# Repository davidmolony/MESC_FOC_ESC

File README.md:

# MESC_FOC_ESC
MESC, Molony ESC, STM32F303 based FOC+BLDC ready, HALL, Encoder, Sensorless, single sides, 2 layer, ~90A @48V

This ESC is intended as a cost optimised alternative to the VESC, by utilising:

Standalone, industry standard footprint gate drivers

Standard D2PAK or H2PAK FETs

Cheap (~2.5$) STM32F303CB microcontroller

Board dimensions 100mmx50mm, so that it can be panelised and manufactured by JLCPCB, or two boards can be combined into one 100mm2 JLCPCB

It is not cross compatible with VESC software, and does not intend to be. VESC has run away with itself in terms of cost, firmware abstraction... in the opinion of this project's author.

# Current Status:  
First build has been made. All functions... function.
Photos in folder! Video of prelim run to be added to Youtube.
Step down works
Step up for Gate drives works
Chip works, all inputs and outputs works
Some concerns about stability of internal opamps... Returning 1.5V instead of 1.6V. First chip soldered returned 1V, and fluctuated by +0.3/-0.1V. 
Motor spins in BLDC mode (6 step) with hall sensors, on Propdrive 2826 1200kV and with APS8072 50kV. Current run up to 20A phase, with minimal PCB heating with no heatsink. Only run to 23V so far, owing to PSU limitation.
FET switching time rather slow with 5 ohm resistors, limiting peak current to 2A (not counting FET and Gate drive resistance) will reduce to 2R7.

# Layout:  
Layout optimised to minimise current loop path, and keep the board completely single sided assembly.

For thermal management, the FETs have vias underneath the drains, which can be interfaced with a heatsink on the PCB underside, using silicone pad/thermal paste & insulator.

# MCU uses:
Timer1 on PA8,9,10 (high) and PB13,14,15 for PWM generation.

Onboard opamps for current sensing and paralelled comparators input on pins PA1,7, PB0.

Phase voltages can be measured on PA3,4,5, or alternatively, digitally read to detect ZC .

Main voltage can be read on PA0.

# Interfaces:
External Interfaces include Hall/Encoder, I2C, PWM in, UART, USB FS.

Hall sensors on Timer4 PB6,7,8, alternatively Encoder can be run on Tim4 PB6,7

Timer3 channel 1 for standard RC PWM input.

USART3 Tx Rx on PB10,11.
USB on PA11,12, with 1k5 pullup to signal FS mode. Canbe used for reflashing (hypothetically).

I2C1 on PA15(SCL) and PB9(SDA), with a plug for a standard SSD1306 breakout. Alternatively, inertial sensor board could be plugged on breakout wire.

Expected BoM cost:  
0.4USD board  
6x2USD FETs  
2.5USD MCU  
3x1USD gate drives  
1USD SMPS converter  
0.4USD inductor  
??? connector cost (dependent on what's fitted, wire in...)  
0.3USD linear reg  
~3USD caps (dependent on how many you want to solder on, which is dependent on distance to battery, desire to comply with EMC, headroom above FET voltage... etc.)  
0.6USD shunts and other resistors  
0.3USD Optional TVS diode, primarily to protect SMPS, which is only rated to 65V  
Total: ~23-24USD

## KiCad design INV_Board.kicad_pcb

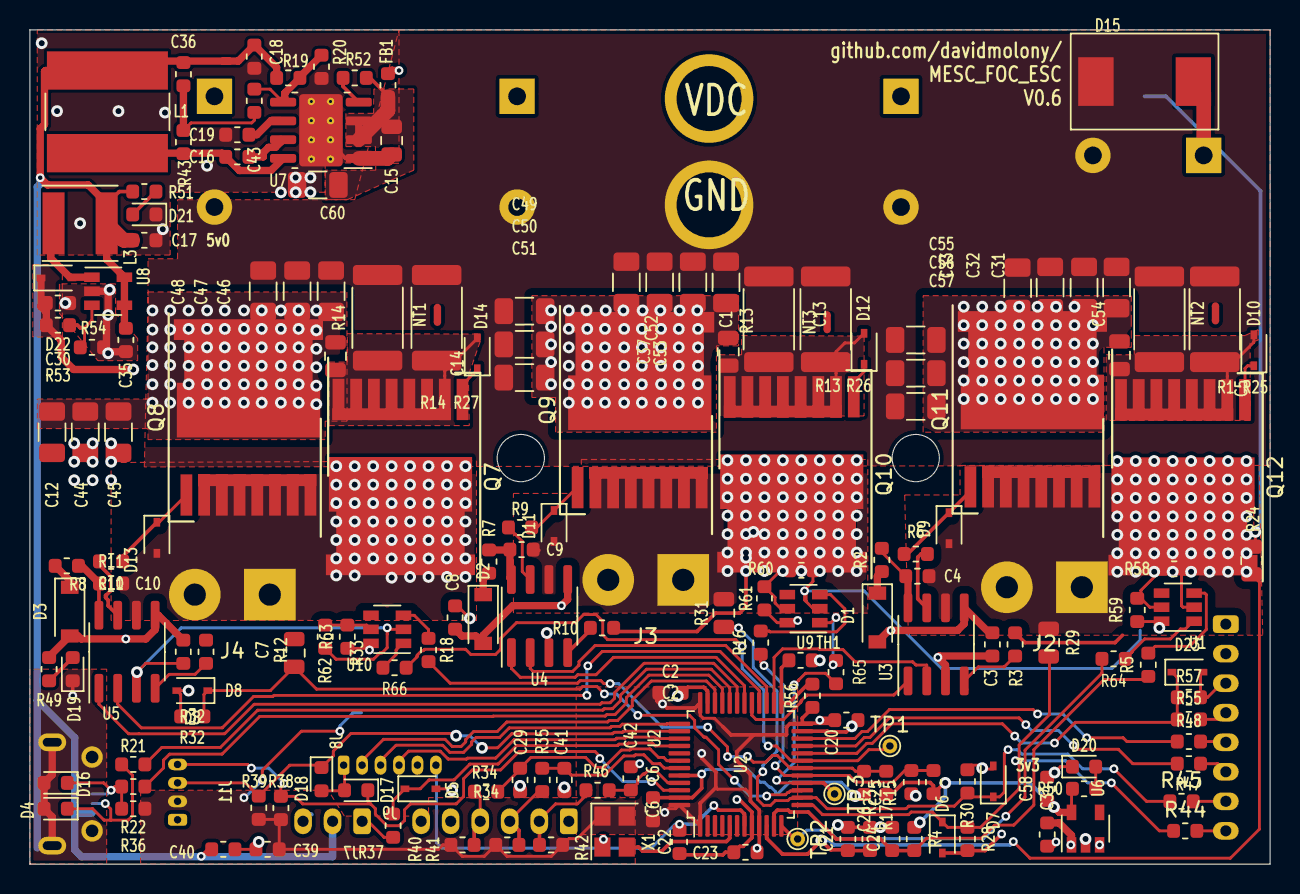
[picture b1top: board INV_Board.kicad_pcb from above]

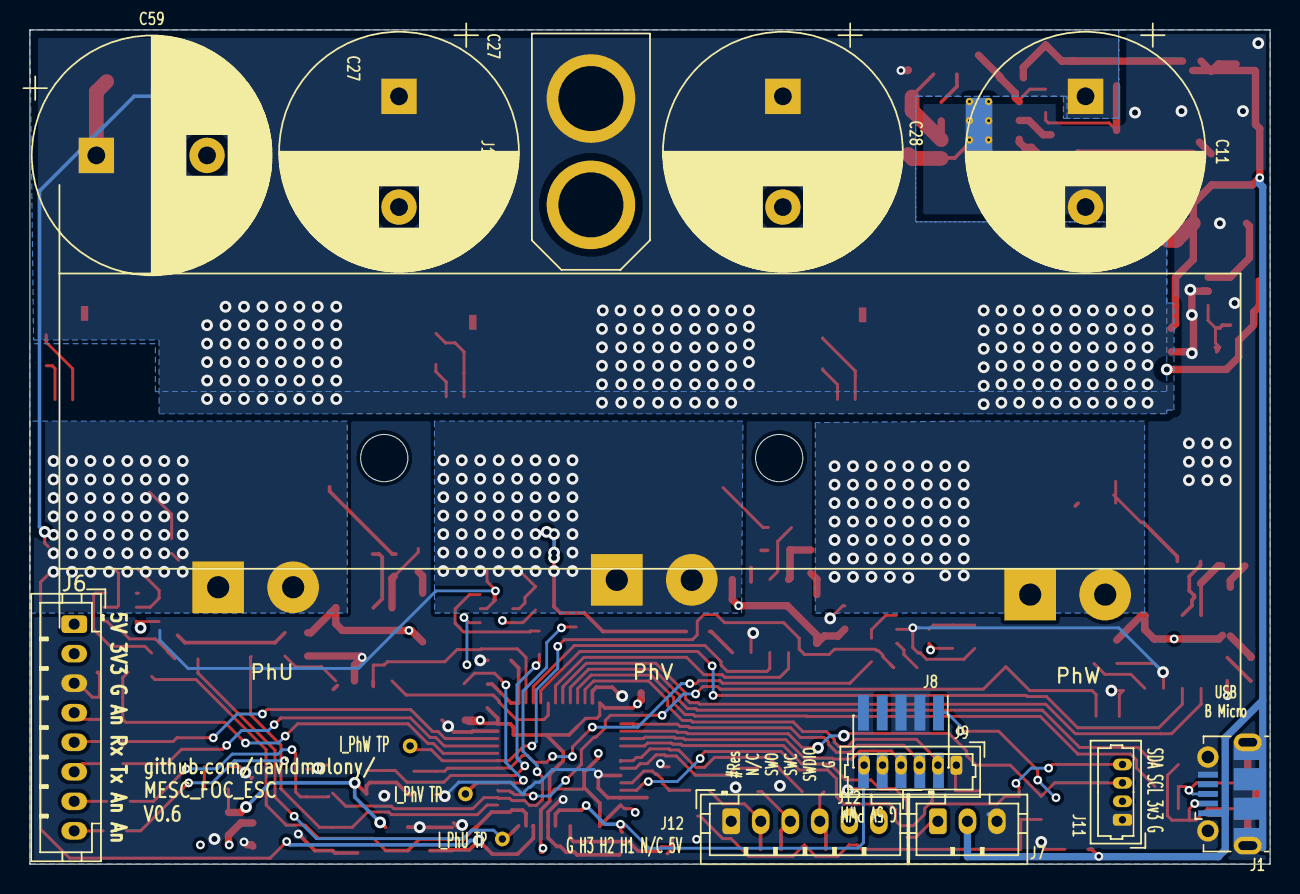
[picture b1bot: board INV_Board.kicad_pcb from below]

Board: 4 copper layers, 84.0 x 56.5 mm, 186 parts (12 on the bottom side), 94 nets.

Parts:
C1, C12, C31, C32, C33, C37, C44, C45, C46, C47, C48, C49, C50, C51, C52, C53, C54, C55, C56, C57, C60: C_1uF 100V; C_1206_3216Metric
C2, C3, C4, C7, C8, C9, C10, C19, C34: C_1uF_25V; C_0603_1608Metric
C5, C13, C14, C15: C_0.1uF_100V; C_0805_2012Metric
C6, C22, C23, C39: C_0.1uF_25V; C_0603_1608Metric
C11, C27, C28, C59: CP_470uF+; CP_Radial_D16.0mm_P7.50mm
C16, C43: C_10nF_16V; C_0603_1608Metric
C17, C18, C20, C30, C35, C40, C58: C_10uF_16V; C_0603_1608Metric
C21, C24, C25, C26, C29, C41, C42: C_100pF_16V; C_0603_1608Metric
C36: C_3nF_16V; C_0603_1608Metric
D1, D2, D3: D_Schottky; D_SOD-123
D4, D16, D17, D18: D_TVS; D_0603_1608Metric
D5, D6, D7, D8, D23: D_Zener_3v3; D_SOD-323
D9, D10, D11, D12, D13, D14: D_Zener_16V; D_SOD-323
D15: D_TVS; DO-214AB
D19, D20, D21: LED_Small; LED_0603_1608Metric
D22: BAT48JFILM; D_SOD-323
FB1: Ferrite_Bead_Small; R_0603_1608Metric
J1: USB_B_Micro; USB_Micro-B_Molex-105017-0001
J2, J3, J4: Conn_01x02_Male; SolderWirePad_1x02_P5.08mm_Drill1.5mm
J6: Conn_01x08_Female; JST_PH_B8B-PH-K_1x08_P2.00mm_Vertical
J7: Conn_01x03_Male; JST_PH_B3B-PH-K_1x03_P2.00mm_Vertical
J8: Conn_ARM_JTAG_SWD_10; PinHeader_2x05_P1.27mm_Vertical_SMD
J9: Conn_01x06_Male; Molex_PicoBlade_53047-0610_1x06_P1.25mm_Vertical
J10: Conn_01x02_Male; XT60
J11: Conn_01x04_Male; Molex_PicoBlade_53047-0410_1x04_P1.25mm_Vertical
J12: Conn_01x06_Female; JST_PH_B6B-PH-K_1x06_P2.00mm_Vertical
L1: L_150uH_1.0A; L_Bourns-SRN8040_8x8.15mm
L3: L_10uH_1A; L_Taiyo-Yuden_NR-50xx
NT1, NT2, NT3: Net-Tie_2; NetTie-2_SMD_Pad0.5mm
Q7, Q8, Q9, Q10, Q11, Q12: IPT015N10N5; Infineon_PG-HSOF-8-1
R1, R13, R14, R25, R26, R27: R_Shunt_1mR; R_2512_6332Metric
R2, R3, R6, R7, R8, R9, R10, R11, R12, R21, R22: R_5; R_0603_1608Metric
R4, R15, R17, R20, R34, R35, R46, R49, R50, R51, R56: R_4k7; R_0603_1608Metric
R5, R16, R18, R54, R64, R65, R66: R_150; R_0603_1608Metric
R19: R_15k; R_0603_1608Metric
R23, R28, R30, R32, R36, R37, R38, R39, R40, R41, R42, R44, R45, R53, R55, R57: R_1k5; R_0603_1608Metric
R24, R29, R31, R33: R_82k; R_0805_2012Metric
R43, R52: R_100k; R_0603_1608Metric
R47, R48: R_100; R_0603_1608Metric
R58, R59, R60, R61, R62, R63: R_30k; R_0603_1608Metric
TH1: Thermistor_NTC; R_0603_1608Metric
TP1, TP2, TP3: TestPoint; TestPoint_THTPad_D1.0mm_Drill0.5mm
U1, U9, U10: INA181; SOT-23-6
U2: STM32F303CBTx; LQFP-48_7x7mm_P0.5mm
U3, U4, U5: IR2181; SOIC-8_3.9x4.9mm_P1.27mm
U6: TPS76333; SOT-23-5
U7: LM5017MR; SOIC-8-1EP_3.9x4.9mm_P1.27mm_EP2.95x4.9mm_Mask2.71x3.4mm_Th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
U8: TPS61041DDC; SOT-23-5
X1: ASE-xxxMHz; Oscillator_SMD_Abracon_ASE-4Pin_3.2x2.5mm

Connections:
#RES: C22.1, J8.10, J9.6, U2.7
+3V3: C2.1, C6.1, C20.1, C23.1, C39.1, C58.1, J6.2, J8.1, J11.2, R4.1, R15.1, R17.1, R36.1, R38.1, R39.1, R40.1, R41.1, R42.1, R50.1, R56.1, R59.1, R61.1, R63.1, U1.6, U2.1, U2.9, U2.24, U2.36, U2.48, U6.5, U9.6, U10.6, X1.1, X1.4
+5V: C17.1, C18.1, C34.1, C35.2, C36.1, C40.1, J1.1, J6.1, J7.2, J12.6, L1.2, L3.1, R19.1, R51.1, U6.1, U6.3, U8.4, U8.5
+12V: C3.1, C7.1, C8.1, C30.1, D1.2, D2.2, D3.2, D22.1, R49.1, R53.2, U3.5, U4.5, U5.5
+VDC: C1.1, C5.1, C11.1, C12.1, C13.1, C14.1, C27.1, C28.1, C31.1, C32.1, C33.1, C37.1, C44.1, C45.1, C46.1, C47.1, C48.1, C49.1, C50.1, C51.1, C52.1, C53.1, C54.1, C55.1, C56.1, C57.1, C59.1, D15.1, FB1.2, J10.2, Q8.3, Q9.3, Q11.3, R24.1
/Hall1: C29.1, R34.1, U2.42
/Hall2: C41.1, R35.1, U2.43
/Hall3: C42.1, R46.1, U2.45
/UGH: D9.1, Q11.1, R6.2
/UGL: D10.1, Q12.1, R3.2
/USBDD+: R22.1, U2.33
/USBDD-: R21.1, U2.32
/VGH: D11.1, Q9.1, R9.2
/VGL: D12.1, Q10.1, R10.2
/WGH: D13.1, Q8.1, R11.2
/WGL: D14.1, Q7.1, R12.2
/op1Vout: R64.1, TP2.1, U2.12
/op2Vout: R65.1, TP3.1, U2.16
/op3Vout: R66.1, TP1.1, U2.19
AnalogIn: D23.1, R55.1, R57.1, U2.20
BoardTemp: R56.2, TH1.1, U2.25
GND: C1.2, C2.2, C3.2, C6.2, C7.2, C8.2, C11.2, C12.2, C15.2, C17.2, C18.2, C19.2, C20.2, C21.2, C22.2, C23.2, C24.2, C25.2, C26.2, C27.2, C28.2, C29.2, C30.2, C31.2, C32.2, C33.2, C34.2, C35.1, C37.2, C39.2, C40.2, C41.2, C42.2, C44.2, C45.2, C46.2, C47.2, C48.2, C49.2, C50.2, C51.2, C52.2, C53.2, C54.2, C55.2, C56.2, C57.2, C58.2, C59.2, C60.1, D4.2, D5.2, D6.2, D7.2, D8.2, D15.2, D16.2, D17.2, D18.2, D19.1, D20.1, D21.1, D23.2, J1.5, J1.6, J6.3, J7.3, J8.3, J8.5, J8.9, J9.1, J10.1, J11.1, J12.1, NT1.2, NT2.2, NT3.2, R1.2, R13.2, R14.2, R20.2, R23.2, R25.2, R26.2, R27.2, R28.2, R30.2, R32.2, R54.2, R57.2, R58.2, R60.2, R62.2, TH1.2, U1.2, U2.8, U2.23, U2.35, U2.44, U2.47, U3.3, U4.3, U5.3, U6.2, U7.1, U7.9, U8.2, U9.2, U10.2, X1.2
I2CSCL: D18.1, J11.3, R39.2, U2.38
I2CSDA: D17.1, J11.4, R38.2, U2.46
ISU: C5.2, D10.2, Q12.2, R1.1, R5.2, R25.1, U1.3
ISU_MCU: C24.1, R4.2, R5.1, U2.11
ISV: C13.2, D12.2, Q10.2, R13.1, R16.2, R26.1, U9.3
ISV_MCU: C25.1, R15.2, R16.1, U2.17
ISW: C14.2, D14.2, Q7.2, R14.1, R18.2, R27.1, U10.3
ISW_MCU: C26.1, R17.2, R18.1, U2.18
unnamed: C4.1, R2.2, U3.8
unnamed: C9.1, R7.2, U4.8
unnamed: C10.1, R8.2, U5.8
unnamed: C15.1, C60.2, FB1.1, R52.2, U7.2, U7.3
unnamed: C16.1, U7.7
unnamed: C16.2, L1.1, R43.2, U7.8
unnamed: C19.1, U7.6
unnamed: C36.2, C43.1, R43.1
unnamed: C43.2, R19.2, R20.1, U7.5
unnamed: D1.1, R2.1
unnamed: D2.1, R7.1
unnamed: D3.1, R8.1
unnamed: D19.2, R49.2
unnamed: D20.2, R50.2
unnamed: D21.2, R51.2
unnamed: D22.2, L3.2, U8.1
unnamed: J6.4, R55.2
unnamed: J6.5, R48.1
unnamed: J6.6, R47.2
unnamed: J6.7, R45.2
unnamed: J6.8, R44.2
unnamed: J7.1, R37.2
unnamed: J12.2, R42.2, R46.2
unnamed: J12.3, R35.2, R41.2
unnamed: J12.4, R34.2, R40.2
unnamed: R3.1, U3.4
unnamed: R6.1, U3.7
unnamed: R9.1, U4.7
unnamed: R10.1, U4.4
unnamed: R11.1, U5.7
unnamed: R12.1, U5.4
unnamed: R52.1, U7.4
unnamed: R53.1, R54.1, U8.3
unnamed: R58.1, R59.2, U1.5
unnamed: R60.1, R61.2, U9.5
unnamed: R62.1, R63.2, U10.5
unnamed: R64.2, U1.1
unnamed: R65.2, U9.1
unnamed: R66.2, U10.1
unnamed: U2.5, X1.3
PWMin: D5.1, R37.1, U2.40
PhaseU: D6.1, R28.1, R29.2, R44.1, U2.13
PhaseV: D7.1, R30.1, R31.2, R45.1, U2.14
PhaseW: D8.1, R32.1, R33.2, U2.15
SGU: NT2.1, U1.4
SGV: NT3.1, U9.4
SGW: NT1.1, U10.4
STRx: R48.2, U2.22
STTx: R47.1, U2.21
SWCLK: J8.4, J9.3, U2.37
SWDIO: J8.2, J9.2, U2.34
SWO: J8.6, J9.4, U2.39
SWU: C4.2, D9.2, J2.1, J2.2, Q11.2, Q12.3, R29.1, U3.6
SWV: C9.2, D11.2, J3.1, J3.2, Q9.2, Q10.3, R31.1, U4.6
SWW: C10.2, D13.2, J4.1, J4.2, Q7.3, Q8.2, R33.1, U5.6
UHin: U2.29, U3.1
ULin: U2.26, U3.2
USBD+: D16.1, J1.3, R22.2, R36.2
USBD-: D4.1, J1.2, R21.2
VHin: U2.30, U4.1
VLin: U2.27, U4.2
Vsense_MCU: C21.1, R23.1, R24.2, U2.10
WHin: U2.31, U5.1
WLin: U2.28, U5.2

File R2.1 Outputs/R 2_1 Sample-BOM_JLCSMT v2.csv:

Comment,Designator,Footprint,LCSC Part #(optional)
10uF 16V,"C17,C18,C20,C30,C40",0603_C,C19702
1uF 25V,"C2,C3,C4,C7,C8,C9,C10,C16,C19,C34",0603_C,C15849
100pF 16V,"C21,C24,C25,C26,C29,C41,C42",0603_C,C14858
0.1uF 25V,"C6,C22,C23,C35,C39",0603_C,C14663
0.01uF 100V,"C36,C37,C38",0805_C,C22423
Zener 16V,"D9,D10,D11,D12,D13,D14",SOD-323_D,C150089
0603 LED,"D19,D20,D21",0603_D,C2286
Schottky diode,D22,SOD-323F_D,C2128
Schottky,"D1,D2,D3",SOD-123FL_D,C64898
Zener_3v3,"D5,D6,D7,D8",SOD-323_D,C145245
MOSFET,"Q1,Q2,Q3,Q4,Q5,Q6",TO263-2_Q,C410926
150?,"R5,R16,R18,R54",0603_R,C22808
15k?,R19,0603_R,C22809
4k7?,"R4,R15,R17,R20,R34,R35,R46,R49,R50,R51",0603_R,C23162
5?,"R2,R3,R6,R7,R8,R9,R10,R11,R12,R21,R22",0603_R,C23164
82k?,"R24,R29,R31,R33",0805_R,C17840
2M?,"R1,R13,R14,R25,R26,R27",2512_R,C60923
1k5?,"R23,R28,R30,R32,R36,R37,R38,R39,R40,R41,R42,R53",0603_R,C22843
1?,"R43,R44,R45",0805_R,C25271
100?,"R47,R48",0603_R,C22775
30k?,R52,0603_R,C22984
STM32F303CB,U2,LQFP-48_7.0x7.0x0.5P,C108516
TPS76333,U6,SOT-323-5_U,C110463
TPS61041DDC,U8,SOT-323-5_U,C7722
OSCILLATORS 8MHz,X1,SMD-OSC-3225_4P,C70556

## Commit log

2020-06-27 Update README.md
    Initial writing of intention, and outline spec.
2020-06-27 Update README.md
    Bizarre and unexpected formatting of initial upload.
2020-06-27 Initial design upload - Full PCB layout with all interfaces - candidate final design.
2020-06-27 Commit changes to put omitted Vias on TVS ground.
2020-06-30 Updates to add extra ceramic caps on power line next to FETs, move high frequency 0805 capacitor to closest position next to FETs, move shunts in a fewmm to reduce inductive current loops, update sch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
2020-07-05 Update to add 5V rail using TPS560430, smaller 3v3 reg, 3v3 pullups and 5V power on hall sensors, tidy up the schematic a bit.
2020-07-09 Tidied up schematic, added snubber pads using 0805 cap and resistor as close as possible to FETs (courtyards infringed, but this is intentional to improve performance), added ferrite bead in front of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
2020-07-10 Change power scheme to have 5V rail genreated from LMR36510, and then boost it up to 12V for the gate drivers, which use very little power. This scheme allows the use of a seperate power source for t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
2020-07-11 Added input resistors on Hall lines, added TVS protection on input lines I2C, USB UART protected with 0402 resistors, since no space... ToDo... fit 0603 or learn to solder 0402... ugh.
2020-07-24 Update R values on power and switch lines to 1k5 and 47k 0805 to enable voltages up to 3.3*48.5/1.5=106V. Add power LEDs and extra 5V cap near USB. Change all text to 0.8mm to make it tidier.
2020-07-25 Added SWO line to the JTAG header to aid debugging and live variable tracking. Will have to manually mod with wire the first set of boards ordered.
2020-08-08 Added pictures, updated readme.
2020-08-08 Add a licence, based on BSD 3 clause with mods to say HARDWARE DESIGN in addition to SOFTWARE, and stipulate that production of the design must have a silkscreen reference to manufacturer and the pro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
2020-09-02 Connectors now JST PH series for throttle and hall sensor input, routing for Iu improved, larger capacitors (2x) 6 pin header to include SWO connectivity, 0402 removed, extra capacitors on Hall senso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
2020-09-09 As ordered R2_2. Updated to use TPS61040 since JLCPCB have them as basic parts plus LM5163 capable, for 100V. XT60 PCB mount connectors, large 16mm diameter caps. 5 samples ordered with CRMicro FETs
2020-10-20 Moved PSU, Added analog in & converted UART to JST PH with VESC pinout, added TP for opamp3, added thermistor, added FAN73901 to the JLCPCB BoM, swapped to LM5017 DCDC, added inductors to BoM, added 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
2020-11-11 Massive redesign of board to have much bigger power paths (3x the copper and shorter returns) anda 66*84 aspect ratio instead of 50*100. Initial positions for INA181 chips put down.
2020-11-20 Provisional rearrangement of board to optimise the layout for power paths in light of Zombies comments, and addition of INA181 opamp options.
2020-11-22 Picture of Ebike...
2020-12-16 As ordered from JLC PCB 15-12-20, external opamps, rerranged for low impedance ground and Vin and moved DCDC. Added optional input analog on phase voltage wires.
2021-01-12 Ringing investigation on the new layout
2021-01-16 Add series resistors to the opamp outputs, this will protect against fighting MCU and ops. Move the Ceramic caps near the DCDC to clear possible top fit capacitors. Increase clearance for different s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
2021-01-16 Optimise layout of DCDC boost to eliminate inducive loop on DCDC, hopefully eliminate ringing.
2021-01-16 Images of burnt BMS FETs
2021-01-16 Pic of boards for Qwerkus and Stancecoke
2021-02-02 Added photos of V0.5 hardware @70A Id 5A Iq
2021-03-28 Generate PDF Schematic
2021-03-28 WIP Rearrange power stage to further reduce inductance and reduce board size by 10mm
2021-04-02 Incomplete smaller, lower inductance option. might not be good since thermal capacit will be reduced.
